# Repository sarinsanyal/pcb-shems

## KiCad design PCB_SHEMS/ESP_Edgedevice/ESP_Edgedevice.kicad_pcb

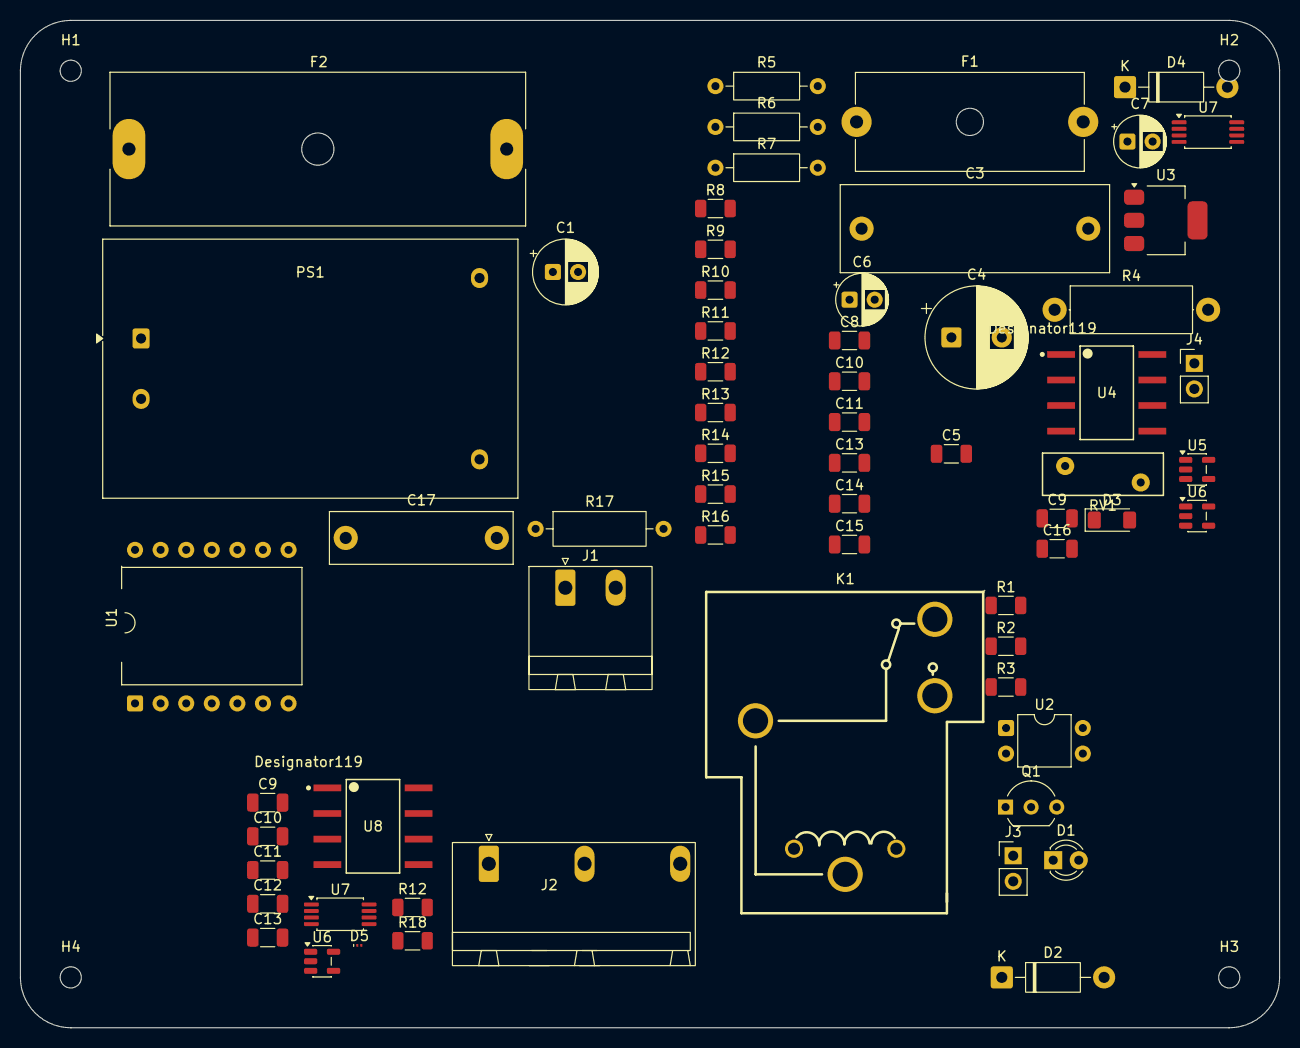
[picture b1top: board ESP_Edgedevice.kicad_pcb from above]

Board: 2 copper layers, 125.0 x 100.0 mm, 68 parts (0 on the bottom side), 41 nets, no tracks yet.

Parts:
C1: 470uF; CP_Radial_D6.3mm_P2.50mm
C3: 470nF X2; C_Rect_L26.5mm_W8.5mm_P22.50mm_MKS4
C4: 470uF; CP_Radial_D10.0mm_P5.00mm
C5: 10uF; C_1206_3216Metric
C6, C7: 10uF; CP_Radial_D5.0mm_P2.50mm
C8: 0.1uF; C_1206_3216Metric
C9, C9#2, C10, C10#2, C11, C11#2, C12, C13, C13#2, C14, C15, C16: 100nF; C_1206_3216Metric
C17: 100nF X2, 275 V AC; C_Rect_L18.0mm_W5.0mm_P15.00mm_FKS3_FKP3
D1: LED; LED_D3.0mm
D2, D4: 1N4007; D_DO-41_SOD81_P10.16mm_Horizontal
D3: 7.5; D_MiniMELF
D5: D_TVS; Nexperia_DSN0603-2_0.6x0.3mm_P0.4mm
F1: 1A,250V AC; Fuseholder_Cylinder-5x20mm_Schurter_0031_8201_Horizontal_Op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
F2: 25A Slow-Blow; Fuseholder_Cylinder-6.3x32mm_Schurter_0031-8002_Horizontal_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
H1, H2, H3, H4: MountingHole; MountingHole_2.1mm
J1: Barrier Terminal; PhoenixContact_MSTBA_2,5_2-G_1x02_P5.00mm_Horizontal
J2: HB9500-9.5-3P; HB9500_9.5-3P
J3: Conn_01x02_Pin; PinHeader_1x02_P2.54mm_Vertical
J4: Conn_01x02; PinHeader_1x02_P2.54mm_Vertical
K1: SLA-05VDC-SL-C; RELAY-TH_SLA-XXVDC-XX-C
PS1: HLK-5M05; Converter_ACDC_Hi-Link_HLK-5Mxx
Q1: S8050; TO-92_Inline_Wide
R1, R3, R11: 1K; R_1206_3216Metric
R2, R12, R15, R18: 1k; R_1206_3216Metric
R4: 220R 1W; R_Axial_DIN0414_L11.9mm_D4.5mm_P15.24mm_Horizontal
R5: 470k; R_Axial_DIN0207_L6.3mm_D2.5mm_P10.16mm_Horizontal
R6, R7: 1M; R_Axial_DIN0207_L6.3mm_D2.5mm_P10.16mm_Horizontal
R8, R9: 100K; R_1206_3216Metric
R10: 220K; R_1206_3216Metric
R12#2: 0.33 Ω, 1206; R_1206_3216Metric
R13, R14, R16: 10k; R_1206_3216Metric
R17: 100R; R_Axial_DIN0309_L9.0mm_D3.2mm_P12.70mm_Horizontal
RV1: Varistor; RV_Disc_D12mm_W4.2mm_P7.5mm
U1: XIAO ESP32C3; XIAO_Socket_W15.24
U2: PC817X3NSZ1B; DIP-4_W7.62mm
U3: AMS1117-5.0; SOT-223-3_TabPin2
U4, U8: AMC1200SDUBR; DUB0008A-IPC_A
U5, U6, U6#2: OPA333xxDBV; SOT-23-5
U7, U7#2: MCP3202; TSSOP-8_4.4x3mm_P0.65mm

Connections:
/+3.3V: C9.1, C10.2, C10#2.2, C11#2.2, C15.2, C16.1, R13.1, R16.1, U1.12 (VCC_3V3), U4.8 (VDD2), U5.5 (V+), U6.5 (V+), U6#2.5 (V+), U7.8 (VDD/VREF), U7#2.8 (VDD/VREF), U8.8 (VDD2)
/Relay/Jd_VCC: D2.1 (K), J3.1, K1.1, U2.4
/Relay/Relay: D2.2 (A), K1.2, Q1.3 (C)
/voltagesensing.kicad_sch/I_ADC: C12.2, R18.2, U7#2.3 (CH1)
/voltagesensing.kicad_sch/I_OUT_P: U6#2.3 (+), U8.7 (VOUTP)
/voltagesensing.kicad_sch/VBIAS: C11.1, R13.2, R14.1, U6.3 (+)
/voltagesensing.kicad_sch/VBIAS_BUF: U6.1, U6.4 (-)
/voltagesensing.kicad_sch/VCC: C9#2.2, U8.1 (VDD1)
/voltagesensing.kicad_sch/VDD1: C6.1, C8.2, R8.1, U3.2 (VO), U4.1 (VDD1)
/voltagesensing.kicad_sch/V_ADC: C13.1, R15.2, U7#2.2 (CH0)
/voltagesensing.kicad_sch/V_OUT_P: U4.7 (VOUTP), U5.3 (+)
COM: C17.2, F2.2, J2.2, K1.3, K1.4
D2: R16.2, U1.3 (D2), U7.1 (~CS/SHDN), U7#2.1 (~CS/SHDN)
D8: U1.9 (D8), U7.7 (CLK), U7#2.7 (CLK)
D9: U1.10 (D9), U7.6 (DOUT), U7#2.6 (DOUT)
D10: U1.11 (D10), U7.5 (DIN), U7#2.5 (DIN)
GND: C1.2, C9.2, C9#2.1, C10.1, C10#2.1, C11.2, C11#2.1, C12.1, C13.2, C13#2.2, C14.2, C15.1, C16.2, D5.2 (A2), J4.2, PS1.3 (-Vout), Q1.1 (E), R1.2, R12#2.2, R14.2, U1.13 (GND), U2.2, U4.5 (GND2), U5.2 (V-), U6.2 (V-), U6#2.2 (V-), U7.4 (VSS), U7#2.4 (VSS), U8.3 (VINN), U8.4 (GND1), U8.5 (GND2)
LIVE: F1.1, F2.1, J1.2, PS1.1 (AC/L)
NC: J2.3, K1.6
NEUTRAL: C4.2, C5.2, C6.2, C7.2, C8.1, D3.2 (A), J1.1, PS1.2 (AC/N), R9.2, RV1.2, U3.1 (GND), U4.4 (GND1)
NO: J2.1, K1.5, R17.1
unnamed: C3.1, R4.2, R5.1
unnamed: C17.1, R17.2
unnamed: D1.1 (K), R1.1
unnamed: C3.2, D3.1 (K), D4.2 (A), R5.2
unnamed: C4.1, C5.1, D4.1 (K), U3.3 (VI)
unnamed: D5.1 (A1), J4.1, R12#2.1, U8.2 (VINP)
unnamed: F1.2, R4.1, R6.1, RV1.1
unnamed: Q1.2 (B), R3.2
unnamed: R2.2, U2.1
unnamed: R3.1, U2.3
unnamed: R6.2, R7.1
unnamed: R7.2, R10.1
unnamed: C7.1, R8.2, R9.1, R11.2, U4.3 (VINN)
unnamed: R10.2, R11.1, U4.2 (VINP)
unnamed: R15.1, U5.1, U5.4 (-)
unnamed: R18.1, U6#2.1, U6#2.4 (-)
unnamed: C13#2.1, U7.2 (CH0)
unnamed: C14.1, R12.1, U7.3 (CH1)
RELAY_IN: D1.2 (A), R2.1, U1.2 (D1)
VCC: C1.1, J3.2, PS1.4 (+Vout), U1.14 (VUSB)
